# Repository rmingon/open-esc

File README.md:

# Open-Source 3-Phase Sensorless ESC Firmware

This is an open-source firmware for controlling 3-phase sensorless BLDC motors using an ATmega88PA microcontroller running at 8 MHz (internal oscillator).  
It is designed for small electric vehicles, drones, robotics, and DIY ESC applications.  
The design uses 6 MOSFETs in a three-phase bridge configuration and includes back-EMF sensing for sensorless commutation.

---

## Features

- Sensorless 6-step (trapezoidal) commutation
- Automatic open-loop startup
- Zero-cross detection via ADC ISR
- Hardware timer-based phase PWM with dead-time
- RC PWM input for speed control
- Optional serial interface (UART) for speed setting
- Direction control and braking support
- Dead-time insertion to prevent MOSFET shoot-through
- Auto-calibrated ADC thresholds for zero-cross detection

---

## Schematic Overview

The system includes the following main blocks:

### Microcontroller

- **ATmega88PA**, powered at 5V using AMS1117-3.3 regulator from +BATT
- Internal 8 MHz oscillator (no external crystal)
- Key pins used:
  - `PD2` → PWM input (from RC receiver)
  - `PD3/PD4/PD5` → High-side MOSFET gates (AH, BH, CH)
  - `PB0/PB1/PB2` → Low-side PWM outputs (AL, BL, CL)
  - `PC0/PC1/PC2` → ADC inputs for Phase A/B/C sensing (A0, A1, A2)

### Power Stage

- 3-phase half-bridge using 6 MOSFETs (Q1–Q6)
- High-side: A03401A
- Low-side: IRLML0030
- Gate resistors to control switching speed and prevent ringing

### Back-EMF Sensing

- Analog divider + DC blocking on each motor phase
- Inputs go to `A0`, `A1`, and `A2`
- Used for zero-cross detection in closed-loop mode

### PWM Input

- Connected to `D2` for RC signal input (standard 1–2 ms pulses)
- Used to control speed and direction
- Interrupt-based decoding for accurate readings

### Serial Debug (optional)

- Via UART (TX/RX, `PD0`/`PD1`)
- Can be used to override speed or monitor state

---

## How to Use

### 1. Assemble the Hardware

- Follow the schematic to build the ESC on a PCB or breadboard
- Ensure proper power filtering (C2, C3–C6)
- Use heatsinks or airflow on the MOSFETs if under heavy load

### 2. Upload Firmware

- Connect AVR ISP programmer to the 6-pin header
- Use [AVRDude](https://www.nongnu.org/avrdude/) or the Arduino IDE
- Ensure fuse bits are set for:
  - Internal 8 MHz clock
  - No clock division
- Upload the `.ino` firmware file

### 3. Calibrate Zero-Crossing (Auto)

- When powered, the firmware automatically calibrates ADC offset thresholds
- Ensure the motor is disconnected or not rotating for accurate calibration

### 4. Run

- Connect an RC receiver or PWM generator to `D2`
- Pulse width controls speed and direction:
  - `< 1480 µs` = reverse
  - `1480–1520 µs` = brake
  - `> 1520 µs` = forward
- Motor will spin up in open-loop mode and switch to sensorless control

### 5. Serial Control (Optional)

- Connect USB-to-serial to TX/RX
- Open serial monitor at `115200 baud`
- Send a value from `0–255` to manually set the speed (for testing/debug)

---

## Motor Braking and Reverse

- Controlled by PWM signal:
  - Brake mode: both high and low sides turned off briefly
  - Reverse: same commutation order but in reverse
- No position feedback required

---

## Dead-Time Handling

- Implemented in software by carefully disabling/enabling high/low MOSFETs with a short delay (a few µs)
- Prevents simultaneous conduction and shoot-through

---

## Files Included

- `ESC_Firmware.ino` – Full firmware with PWM control, ISR ADC, RC interface
- `README.md` – Project documentation
- Schematic (`.png`) – Visual hardware design

---

## Supported Microcontrollers

- ATmega88PA (default)
- Can be ported to ATmega328P with minimal changes

---

## Test Points

- TP1–TP3: Phase voltages for probing/debug
- TP6: PWM input
- TP5: GND
- TP4: +BATT

---

## Pictures

---

## Safety Notes

- Always test with low-voltage supply first
- Double-check gate drive signals with oscilloscope
- Use overcurrent and overtemperature protection externally if needed

---

## License

MIT License — You can freely use, modify, and distribute this project.

---

## Author

Created by [Your Name / GitHub Handle]  
Feel free to fork, improve, and contribute via pull requests!

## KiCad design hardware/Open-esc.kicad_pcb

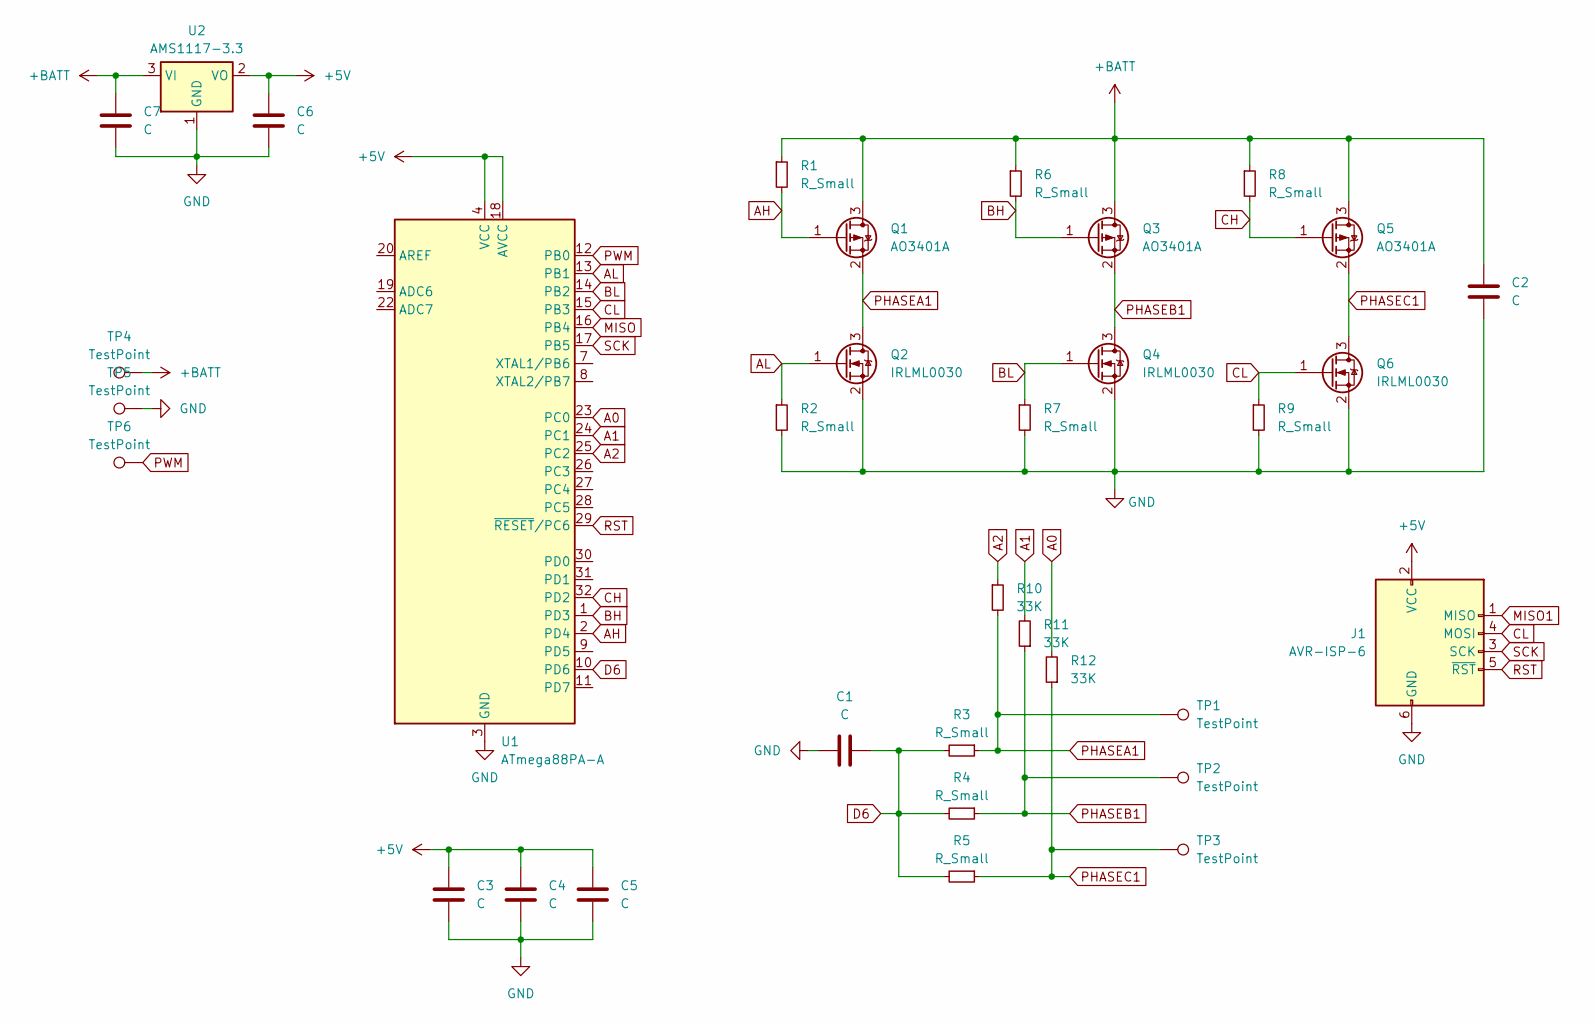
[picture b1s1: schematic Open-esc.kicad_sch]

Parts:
C1, C2, C3, C4, C5, C6, C7: C; C_0603_1608Metric
J1: AVR-ISP-6; PinHeader_2x03_P1.00mm_Vertical
Q1, Q3, Q5: AO3401A; SOT-23
Q2, Q4, Q6: IRLML0030; SOT-23
R1, R2, R3, R4, R5, R6, R7, R8, R9: R_Small; R_0603_1608Metric
R10, R11, R12: 33K; R_0603_1608Metric
TP1, TP2, TP3: TestPoint; TestPoint_Pad_2.0x2.0mm
TP4, TP5, TP6: TestPoint; TestPoint_Pad_4.0x4.0mm
U1: ATmega88PA-A; TQFP-32_7x7mm_P0.8mm
U2: AMS1117-3.3; SOT-223-3_TabPin2

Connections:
+5V: C3.1, C4.1, C5.1, C6.1, J1.2 (VCC), U1.4 (VCC), U1.6 (VCC), U1.18 (AVCC), U2.2 (VO)
+BATT: C2.1, C7.1, Q1.3 (D), Q3.3 (D), Q5.3 (D), R1.1, R6.1, R8.1, TP4.1, U2.3 (VI)
A0: R12.2, U1.23 (PC0)
A1: R11.2, U1.24 (PC1)
A2: R10.1, U1.25 (PC2)
AH: Q1.1 (G), R1.2, U1.2 (PD4)
AL: Q2.1 (G), R2.1, U1.13 (PB1)
BH: Q3.1 (G), R6.2, U1.1 (PD3)
BL: Q4.1 (G), R7.1, U1.14 (PB2)
CH: Q5.1 (G), R8.2, U1.32 (PD2)
CL: J1.4 (MOSI), Q6.1 (G), R9.1, U1.15 (PB3)
D6: C1.2, R3.2, R4.2, R5.2, U1.10 (PD6)
GND: C1.1, C2.2, C3.2, C4.2, C5.2, C6.2, C7.2, J1.6 (GND), Q2.2 (S), Q4.2 (S), Q6.2 (S), R2.2, R7.2, R9.2, TP5.1, U1.3 (GND), U1.5 (GND), U1.21 (GND), U2.1 (GND)
MISO: U1.16 (PB4)
MISO1: J1.1 (MISO)
PHASEA1: Q1.2 (S), Q2.3 (D), R3.1, R10.2, TP1.1
PHASEB1: Q3.2 (S), Q4.3 (D), R4.1, R11.1, TP2.1
PHASEC1: Q5.2 (S), Q6.3 (D), R5.1, R12.1, TP3.1
PWM: TP6.1, U1.12 (PB0)
RST: J1.5 (~RST), U1.29 (~RESET/PC6)
SCK: J1.3 (SCK), U1.17 (PB5)

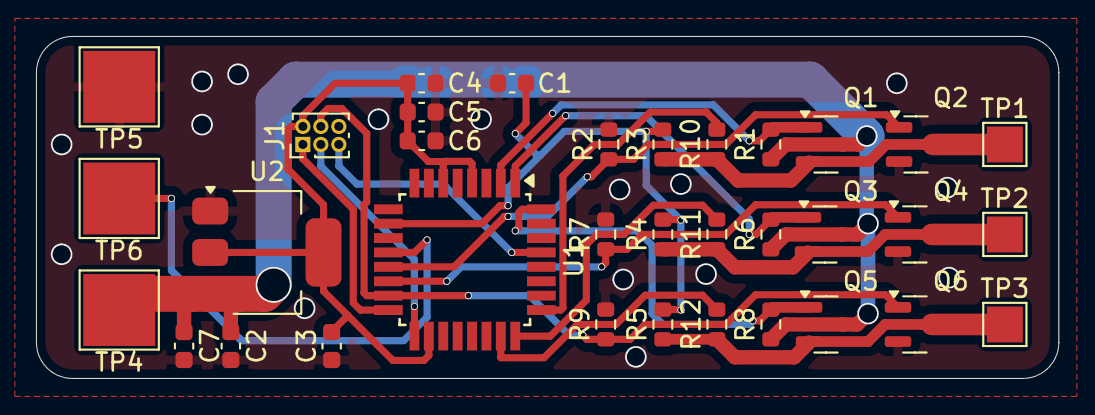
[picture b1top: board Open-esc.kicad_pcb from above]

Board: 2 copper layers, 56.8 x 19.0 mm, 34 parts (0 on the bottom side), 19 nets.

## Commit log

2025-05-14 add schematic
2025-05-14 wiring phase
2025-05-15 rename connection and add pad wiring
2025-05-15 add pictures
2025-05-15 add readme
2025-05-15 add general gnd
2025-05-15 add firmware code
2025-05-17 update rst pin
